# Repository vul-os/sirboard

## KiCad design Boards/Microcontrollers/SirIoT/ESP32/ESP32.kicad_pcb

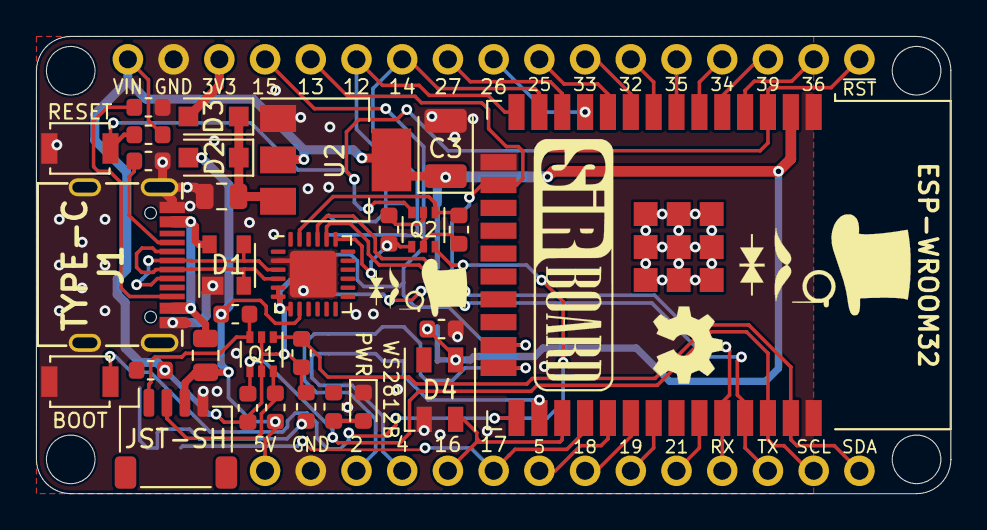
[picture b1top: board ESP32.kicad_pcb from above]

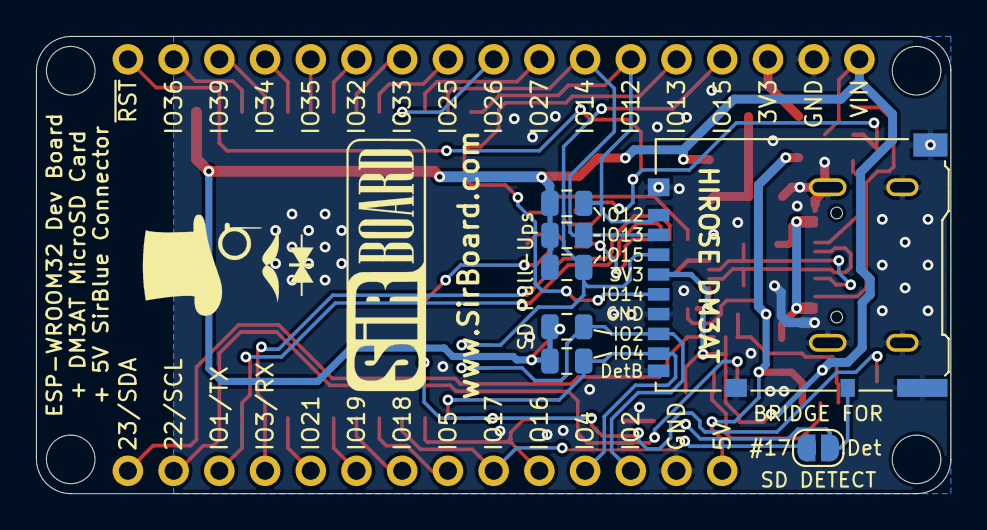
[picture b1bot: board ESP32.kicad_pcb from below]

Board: 2 copper layers, 50.8 x 25.4 mm, 43 parts (9 on the bottom side), 45 nets.

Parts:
BOOT: SW_Push; SW_SPST_B3U-1000P
C2: 10uF; C_0805_2012Metric
C3: 100uF; CP_EIA-3528-21_Kemet-B
C4: 1uF; C_0603_1608Metric
CARD1: SolderJumper_2_Open; SolderJumper-2_P1.3mm_Open_RoundedPad1.0x1.5mm
D1: PRTR5V0U2X; SOT-143
D2, D3: MBR120; D_SOD-123F
D4: WS2812B; WS2812B_MINI
DNP1, DNP2, DNP3, DNP4, DNP5: 47k; R_0805_2012Metric
F1: 500mA; Fuse_0805_2012Metric
H1, H2, H3, H4: MountingHole; MountingHole_2.7mm_M2.5
J1: TYPE-C; USB_C
J2: Micro_SD_Card_Det_Hirose_DM3AT; microSD_Hirose_DM3AT
J4: Conn_01x14; PinHeader_1x14_P2.54mm_Vertical
J5: Conn_01x17; PinHeader_1x17_P2.54mm_Vertical
JST-SH: SirBlue; SirBlue_Connector
PWR: RED; LED_0603_1608Metric
Q1: BSS138DW; SOT-363_SC-70-6
Q2: MMBT2222A; SOT-363_SC-70-6
R1, R2: 5K1; R_0603_1608Metric
R4, R5, R6, R7, R8, R9, R14, R17, R18: 10k; R_0603_1608Metric
R16: 1K; R_0603_1608Metric
RESET: SW_Push; SW_SPST_B3U-1000P
U1: CP2104; QFN-24-1EP_4x4mm_P0.5mm_EP2.6x2.6mm
U2: AZ1117-3.3; SOT-223-3_TabPin2
U3: ESP32-WROOM-32D; ESP32-WROOM-32

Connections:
#RST: J5.17, Q2.3, R14.2, RESET.1, U3.3
+3V3: C3.1, C4.1, D4.1, DNP1.1, DNP2.1, DNP3.1, DNP4.1, DNP5.1, J2.4, J5.1, Q1.2, Q1.5, R4.1, R6.1, R14.1, R16.1, R17.2, R18.2, U1.5, U1.6, U1.7, U2.2, U3.2
/CARD_DETECT: CARD1.2, J2.10, R17.1
/CC1: J1.A5, R2.1
/CC2: J1.B5, R1.1
D+: D1.3, J1.A6, J1.B6, U1.3
D-: D1.2, J1.A7, J1.B7, U1.4
DTR: Q2.1, R9.1, U1.23
GND: BOOT.1, C2.2, C3.2, C4.2, D1.1, D4.3, J1.A1, J1.A12, J1.B1, J1.B12, J1.S1, J2.6, J2.9, J2.11, J4.2, J5.2, JST-SH.4, PWR.1, R1.2, R2.2, RESET.2, U1.2, U1.25, U2.1, U3.1, U3.15, U3.38
IO0: BOOT.2, Q2.6, R18.1, U3.25
IO1_TX: J4.12, U1.20, U3.35
IO2_SD_D0: DNP2.2, J2.7, J4.3, U3.24
IO3_RX: J4.11, U1.21, U3.34
IO4_SD_D1: DNP1.2, J2.8, J4.4, U3.26
IO5_SD_CS: J4.7, U3.29
IO12_SD_D2: DNP5.2, J2.1, J5.6, U3.14
IO13_SD_D3: DNP4.2, J2.2, J5.7, U3.13
IO14_SD_CLK: J2.5, J5.5, U3.16
IO15_SD_CMD: DNP3.2, J2.3, J5.4, U3.23
IO16: D4.4, J4.5, U3.27
IO17_SD_DET: CARD1.1, J4.6, U3.28
IO18: J4.8, U3.30
IO19: J4.9, U3.31
IO21: J4.10, U3.33
IO22_SCL: J4.13, Q1.4, R6.2, U3.36
IO23_SDA: J4.14, Q1.1, R4.2, U3.37
IO25: J5.10, U3.10
IO26: J5.9, U3.11
IO27: J5.8, U3.12
IO32: J5.12, U3.8
IO33: J5.11, U3.9
IO34: J5.14, U3.6
IO35: J5.13, U3.7
IO36: J5.16, U3.4
IO39: J5.15, U3.5
unnamed: C2.1, D2.1, D3.1, U2.3
unnamed: PWR.2, R16.2
unnamed: Q2.2, R8.2
unnamed: Q2.5, R9.2
RTS: Q2.4, R8.1, U1.19
SCL_5V: JST-SH.1, Q1.3, R7.1
SDA_5V: JST-SH.2, Q1.6, R5.1
VBUS: D2.2, F1.2, J4.1, JST-SH.3, R5.2, R7.2, U1.8
VIN: D3.2, J5.3
VUSB: D1.4, F1.1, J1.A4, J1.A9, J1.B4, J1.B9

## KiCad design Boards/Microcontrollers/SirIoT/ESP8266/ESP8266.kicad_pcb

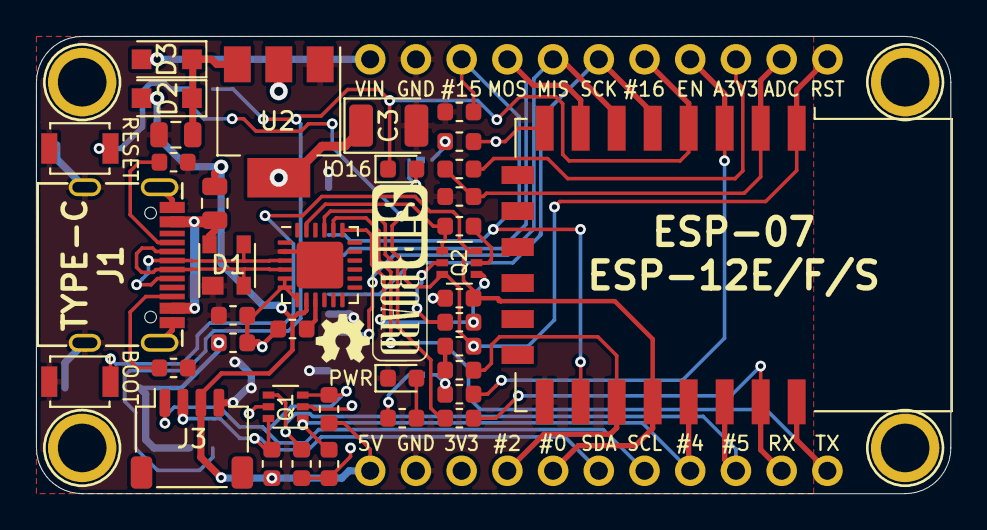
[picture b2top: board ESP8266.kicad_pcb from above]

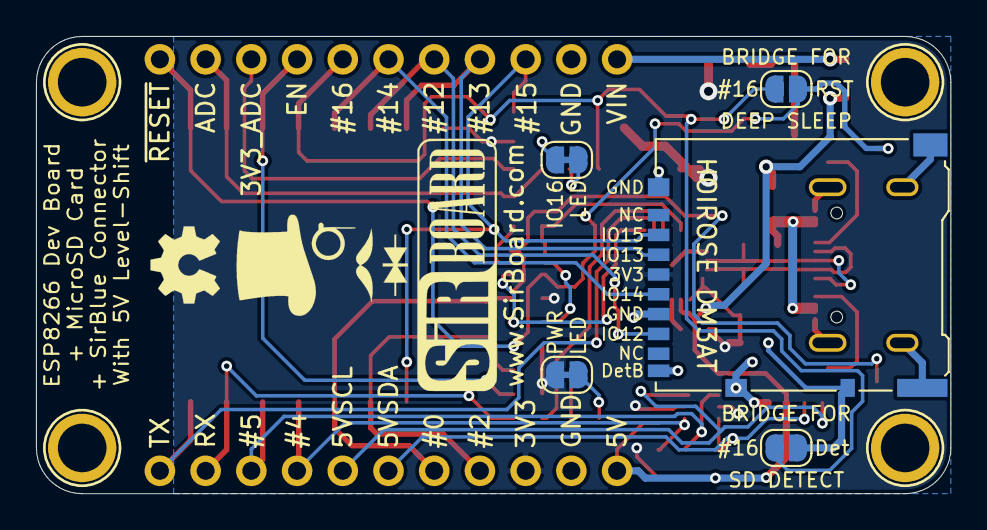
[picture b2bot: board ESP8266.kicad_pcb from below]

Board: 2 copper layers, 50.8 x 25.4 mm, 49 parts (7 on the bottom side), 38 nets.

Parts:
BOOT: SW_Push; SW_SPST_B3U-1000P
C1: 100nF; C_0603_1608Metric
C2: 10uF; C_0805_2012Metric
C3: 100uF; CP_EIA-3528-21_Kemet-B
CARD1: SolderJumper_2_Open; SolderJumper-2_P1.3mm_Open_RoundedPad1.0x1.5mm
D1: PRTR5V0U2X; SOT-143
D2, D3: MBR120; D_SOD-123F
F1: 500mA; Fuse_0805_2012Metric
H1, H2, H3, H4: MountingHole; MountingHole_M2.5_SirBoard
HOIROSE DM3AT: Micro_SD_Card_Det_Hirose_DM3AT; microSD_Hirose_DM3AT
IO16: LED_DELETE2; SolderJumper-2_P1.3mm_Bridged_RoundedPad1.0x1.5mm
IO16#2: BLUE; LED_0603_1608Metric
J1: TYPE-C; USB_C
J3: SirBlue; SirBlue_Connector
J4, J6: Conn_01x11; PinHeader_1x11_P2.54mm_Vertical
PWR: LED_DELETE1; SolderJumper-2_P1.3mm_Bridged_RoundedPad1.0x1.5mm
PWR#2: RED; LED_0603_1608Metric
Q1: BSS138DW; SOT-363_SC-70-6
Q2: MMBT2222A; SOT-363_SC-70-6
R1, R2: 5K1; R_0603_1608Metric
R3: 4K7; R_0603_1608Metric
R4, R5, R6, R7, R8, R9, R10, R11, R14, R17, R18: 10k; R_0603_1608Metric
R12, R15, R16: 1K; R_0603_1608Metric
R13: 10K; R_0603_1608Metric
R19: 220K; R_0603_1608Metric
R20: 100K; R_0603_1608Metric
RESET: SW_Push; SW_SPST_B3U-1000P
SLEEP1: SolderJumper_2_Open; SolderJumper-2_P1.3mm_Open_RoundedPad1.0x1.5mm
U1: CP2104; QFN-24-1EP_4x4mm_P0.5mm_EP2.6x2.6mm
U2: AZ1117-3.3; SOT-223-3_TabPin2
U3: ESP-12F; ESP-12E

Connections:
#RST: J6.11, Q2.3, R14.2, RESET.1, SLEEP1.2, U3.1
+3V3: C1.1, C3.1, HOIROSE DM3AT.4, J4.3, PWR.1, Q1.2, Q1.5, R3.2, R4.1, R6.1, R10.2, R11.2, R14.1, R15.1, R17.1, R18.2, U1.5, U1.6, U1.7, U2.2, U3.8
/CARD_DETECT: CARD1.2, HOIROSE DM3AT.10, R17.2
/CC1: J1.A5, R2.1
/CC2: J1.B5, R1.1
/RST: R3.1, U1.9
ADC: J6.10, R19.1, R20.2, U3.2
ADC_3V3: J6.9, R19.2
D+: D1.3, J1.A6, J1.B6, U1.3
D-: D1.2, J1.A7, J1.B7, U1.4
DTR: Q2.1, R9.1, U1.23
EN: J6.8, R10.1, U3.3
GND: BOOT.1, C1.2, C2.2, C3.2, D1.1, HOIROSE DM3AT.6, HOIROSE DM3AT.9, HOIROSE DM3AT.11, J1.A1, J1.A12, J1.B1, J1.B12, J1.S1, J3.4, J4.2, J6.2, PWR#2.1, R1.2, R2.2, R13.1, R20.1, RESET.2, U1.2, U1.25, U2.1, U3.15
GPIO0: BOOT.2, J4.5, Q2.6, R18.1, U3.18
GPIO2: J4.4, R11.1, U3.17
GPIO12_MISO: HOIROSE DM3AT.7, J6.5, U3.6
GPIO13_MOSI: HOIROSE DM3AT.3, J6.4, U3.7
GPIO14_SCK: HOIROSE DM3AT.5, J6.6, U3.5
GPIO15: HOIROSE DM3AT.2, J6.3, R13.2, U3.16
GPIO16: CARD1.1, IO16#2.1, J6.7, SLEEP1.1, U3.4
unnamed: C2.1, D2.1, D3.1, U2.3
unnamed: PWR.2, R16.1
unnamed: IO16.1, R15.2
unnamed: IO16.2, IO16#2.2
unnamed: PWR#2.2, R16.2
unnamed: Q2.2, R8.2
unnamed: Q2.5, R9.2
RTS: Q2.4, R8.1, U1.19
RXD: J4.10, R12.2, U3.21
RX_ESP: R12.1, U1.21
SCL_3V3: J4.9, Q1.4, R6.2, U3.20
SCL_5V: J3.1, J4.7, Q1.3, R7.1
SDA_3V3: J4.8, Q1.1, R4.2, U3.19
SDA_5V: J3.2, J4.6, Q1.6, R5.1
TX_ESP: J4.11, U1.20, U3.22
VBUS: D2.2, F1.2, J3.3, J4.1, R5.2, R7.2, U1.8
VIN: D3.2, J6.1
VUSB: D1.4, F1.1, J1.A4, J1.A9, J1.B4, J1.B9

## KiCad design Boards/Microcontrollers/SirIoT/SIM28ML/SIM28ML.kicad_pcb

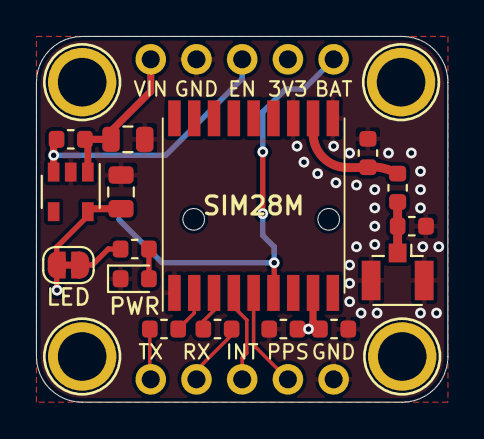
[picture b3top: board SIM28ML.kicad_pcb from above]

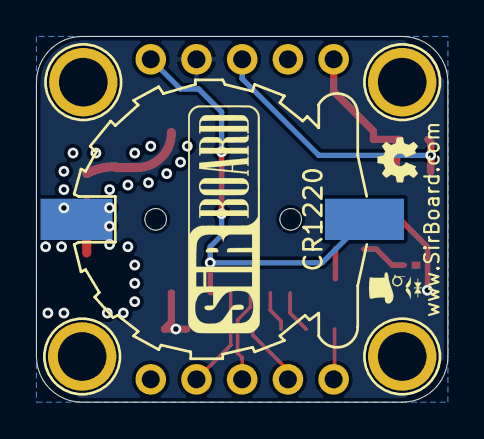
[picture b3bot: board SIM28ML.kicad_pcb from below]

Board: 2 copper layers, 22.9 x 20.3 mm, 23 parts (3 on the bottom side), 15 nets.

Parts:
AE1: Antenna_Shield; U.FL_Hirose_U.FL-R-SMT-1_Vertical
BT1: Battery_Cell; S8411-45R_1
C1: 4.7uF; C_0603_1608Metric
C2: 100nF; C_0603_1608Metric
C3, C4: 10uF; C_0805_2012Metric
C5, C7: NC; C_0603_1608Metric
H1, H2, H3, H4: MountingHole; MountingHole_M2.5_SirBoard
IC1: SIM28M
J1, J2: Conn_01x05; PinHeader_1x05_P2.54mm_Vertical
JP2: SolderJumper_2_Bridged; SolderJumper-2_P1.3mm_Bridged_RoundedPad1.0x1.5mm
PWR: LED; LED_0603_1608Metric
R1, R2: 100R; R_0603_1608Metric
R3: 10K; R_0603_1608Metric
R4: 0R; R_0603_1608Metric
R6: 680E; R_0603_1608Metric
U1: AP2127K-3.3; SOT-23-5

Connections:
3V3: C1.1, C2.1, C4.1, IC1.8, J2.4, JP2.1, U1.5
/ANT: C5.1, IC1.11, R4.1
EN: J2.3, R3.2, U1.3
GND: AE1.2, BT1.2, C1.2, C2.2, C3.2, C4.2, C5.2, C7.2, IC1.1, IC1.10, IC1.12, J1.5, J2.2, PWR.1, U1.2
INT: IC1.5, J1.4
unnamed: AE1.1, C7.1, R4.2
unnamed: PWR.2, R6.1
unnamed: IC1.2, R2.2
unnamed: IC1.3, R1.2
unnamed: JP2.2, R6.2
PPS: IC1.4, J1.3
RXD0: J1.2, R1.1
TXD0: J1.1, R2.1
VBAT: BT1.1, IC1.6, J2.5
VIN: C3.1, J2.1, R3.1, U1.1

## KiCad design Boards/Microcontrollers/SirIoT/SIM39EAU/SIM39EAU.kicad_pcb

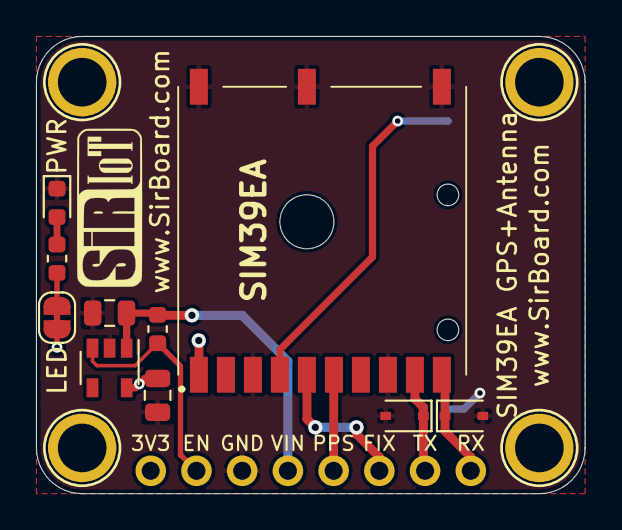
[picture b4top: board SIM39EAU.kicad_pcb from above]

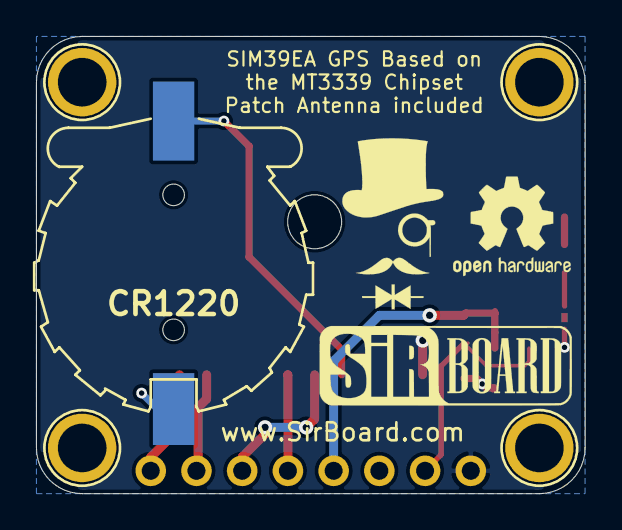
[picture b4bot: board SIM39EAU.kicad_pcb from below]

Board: 2 copper layers, 30.5 x 25.4 mm, 16 parts (2 on the bottom side), 11 nets.

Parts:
C3, C4: 10uF; C_0805_2012Metric
CR1220: CR1220; S8411-45R_1
D1, D2: TVS; D_SOD-323
H1, H2, H3, H4: MountingHole; MountingHole_M2.5_SirBoard
J1: Conn_01x08; PinHeader_1x08_P2.54mm_Vertical
LED: SolderJumper_2_Bridged; SolderJumper-2_P1.3mm_Bridged_RoundedPad1.0x1.5mm
PWR: LED; LED_0603_1608Metric
R1: 680E; R_0603_1608Metric
R3: 10K; R_0603_1608Metric
SIM39EA: SIM39EA
U1: AP2127K-3.3; SOT-23-5

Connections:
3V3: C4.1, J1.8, LED.1, SIM39EA.1, U1.5
EN: J1.7, R3.2, U1.3
FIX: J1.3, SIM39EA.5
GND: C3.2, C4.2, CR1220.2, D1.2, D2.2, J1.6, PWR.1, SIM39EA.3, SIM39EA.8, SIM39EA.11, SIM39EA.12, SIM39EA.13, U1.2
unnamed: CR1220.1, SIM39EA.4
unnamed: PWR.2, R1.1
unnamed: LED.2, R1.2
PPS: J1.4, SIM39EA.6
RX: D1.1, J1.1, SIM39EA.10
TX: D2.1, J1.2, SIM39EA.9
VIN: C3.1, J1.5, R3.1, U1.1

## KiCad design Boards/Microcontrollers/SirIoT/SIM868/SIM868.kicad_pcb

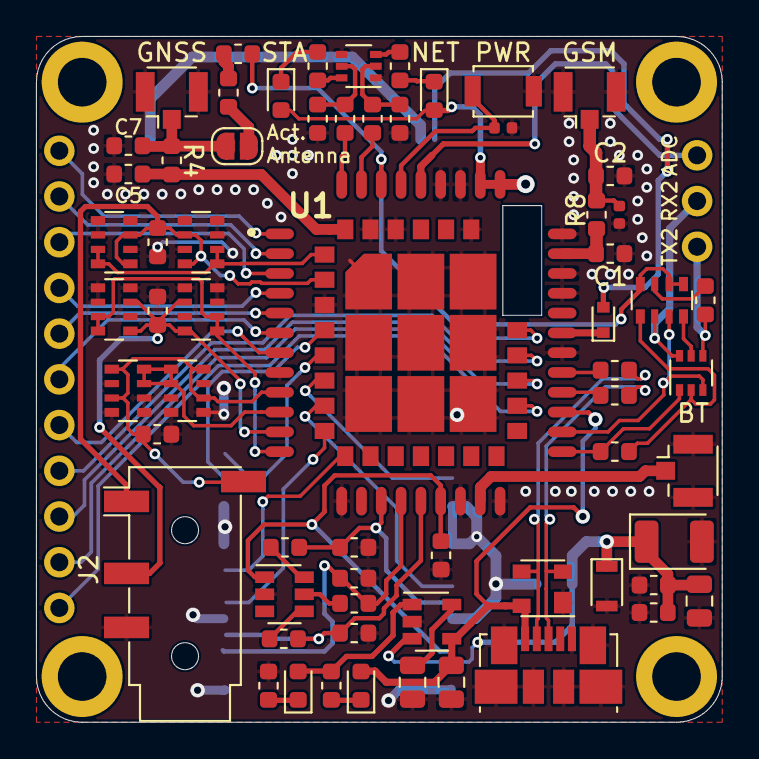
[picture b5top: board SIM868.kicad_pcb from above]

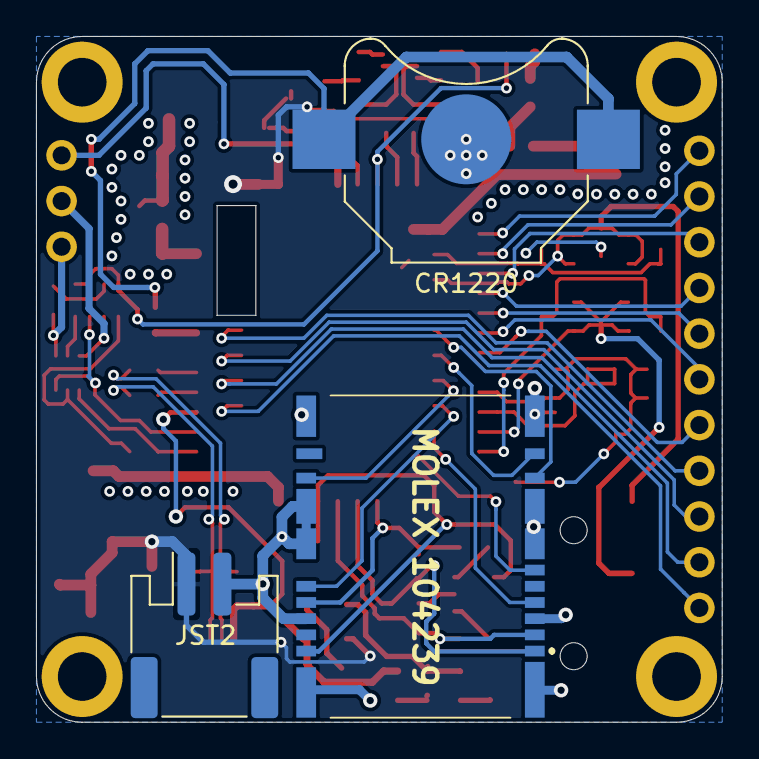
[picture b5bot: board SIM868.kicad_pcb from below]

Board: 2 copper layers, 38.1 x 38.1 mm, 73 parts (5 on the bottom side), 68 nets.

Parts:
BT: Antenna_Shield; U.FL_Hirose_U.FL-R-SMT-1_Vertical
C1, C2, C5, C7: NC; C_0603_1608Metric
C3: 100nF; C_0603_1608Metric
C4: 100uF; CP_EIA-3528-21_Kemet-B
C6: 10uF; C_0805_2012Metric
C8: 33pF; C_0603_1608Metric
C9: 10pF; C_0603_1608Metric
C10, C11, C12: 22pF; C_0603_1608Metric
C13: 1uF; C_0805_2012Metric
CN1, CN2, CN3: 10pF; R_Array_Convex_4x0603
CN4, CN5, CN6: 33pF; R_Array_Convex_4x0603
CR1220: CR1025; BatteryHolder_Keystone_3000_1x12mm
D1: ESDA6V1-5SC6; SOT-23-6
D3: D_Schottky; D_SOD-523
D5: ORANGE; LED_0603_1608Metric
D6: GREEN; LED_0603_1608Metric
D7: PRTR5V0U2X; SOT-143
D9, D11, D13: BDFN1C031V; C_0603_1608Metric
GNSS: Antenna_Shield; U.FL_Hirose_U.FL-R-SMT-1_Vertical
GSM: Antenna_Shield; U.FL_Hirose_U.FL-R-SMT-1_Vertical
H1, H2, H3, H4: MountingHole; MountingHole_2.7mm_M2.5_ISO14580_Pad
J2: AudioJack4; Jack_3.5mm_PJ320D_Horizontal
J4: USB_B_Micro; USB_Micro-B_Molex_47346-0001
J5: Conn_01x11; PinHeader_1x11_P2.54mm_Vertical
J6: Conn_01x03; PinHeader_1x03_P2.54mm_Vertical
JP1: SolderJumper_2_Open; SolderJumper-2_P1.3mm_Open_RoundedPad1.0x1.5mm
JST2: Conn_01x02; JST_PH_S2B-PH-SM4-TB_1x02-1MP_P2.00mm_Horizontal
L1: 27n; L_0603_1608Metric
MOLEX 104239: MOLEX 104239-1430; 1042391430
NET: WHITE; LED_0603_1608Metric
PWR: B3U-1000P; SW_SPST_B3U-1000P
Q1, Q2: BC847BDW1; SOT-363_SC-70-6
R1, R6, R13, R16: 47K; R_0603_1608Metric
R2: 2K; R_0805_2012Metric
R3, R14, R17: 1K; R_0603_1608Metric
R4, R8: 0R; R_0603_1608Metric
R5: 10R; R_0603_1608Metric
R7: 470E; R_0603_1608Metric
R9, R10, R11: 51E; R_0603_1608Metric
R12, R15: 4K7; R_0603_1608Metric
R18, R19: 22E; R_0603_1608Metric
RN2: 4k7; R_Array_Convex_4x0603
STA: WHITE; LED_0603_1608Metric
TVS1, TVS2: LXES15AAA1-153; R_0402_1005Metric
U1: SIM868
U2: MCP73831-2-OT; SOT-23-5
Z1: PZ3D4V2H; D_SOD-323F

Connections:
5V: R6.2, RN2.7
/BT: BT.1, U1.20
/uD+: R18.1, U1.25
/uD-: R19.1, U1.26
ADC: J6.3, U1.38
D+: D7.2, J4.3, R18.2
D-: D7.3, J4.2, R19.2
GND: BT.2, C1.2, C2.2, C3.2, C4.2, C5.2, C6.2, C7.2, C8.2, C9.2, C10.2, C11.2, C12.2, C13.2, CN1.2, CN1.4, CN1.5, CN1.6, CN2.2, CN2.4, CN2.5, CN2.6, CN3.2, CN3.4, CN3.5, CN3.6, CN4.3, CN4.4, CN4.5, CN4.7, CN5.3, CN5.4, CN5.5, CN5.7, CN6.3, CN6.4, CN6.5, CN6.7, CR1220.2, D1.2, D7.1, D9.1, D11.1, D13.1, GNSS.2, GSM.2, J2.R2, J4.5, J4.6, JST2.2, MOLEX 104239.4, MOLEX 104239.12, MOLEX 104239.15, MOLEX 104239.16, MOLEX 104239.17, MOLEX 104239.18, MOLEX 104239.19, MOLEX 104239.20, MOLEX 104239.21, MOLEX 104239.22, PWR.1, Q2.1, Q2.4, R2.1, R3.2, R13.1, R16.1, TVS1.1, TVS2.1, U1.8, U1.13, U1.19, U1.21, U1.27, U1.30, U1.31, U1.33, U1.36, U1.37, U1.45, U1.63, U1.66, U1.67, U1.69, U1.70, U1.71, U1.72, U1.73, U1.74, U1.75, U1.76, U1.77, U2.2, Z1.2
GNSS_ANT: C5.1, R4.1, U1.68
GNSS_EN: J5.11, U1.59
GNSS_RX: J5.8, U1.62
GNSS_TX: J5.9, U1.61
GSM_ANT: C1.1, R8.1, U1.32
MIC+: CN1.1, CN1.3, CN4.6, CN4.8, D11.2, J2.S, U1.9
MIC-: CN1.7, CN1.8, CN4.1, CN4.2, U1.10
NET_L: R12.2, U1.41
unnamed: C7.1, GNSS.1, JP1.2, R4.2
unnamed: C2.1, GSM.1, R8.2, TVS2.2
unnamed: CR1220.1, D3.2
unnamed: D1.4, R9.1
unnamed: D1.5, R10.1
unnamed: D1.6, R11.1
unnamed: R14.2, STA.1
unnamed: D3.1, U1.28
unnamed: NET.1, R17.2
unnamed: D5.1, R7.2
unnamed: D6.1, R3.1
unnamed: D6.2, R7.1, U2.1
unnamed: JP1.1, L1.1
unnamed: L1.2, R5.2
unnamed: Q1.2, R1.2, RN2.1
unnamed: Q1.5, RN2.4
unnamed: Q2.2, R12.1, R13.2
unnamed: Q2.3, R17.1
unnamed: Q2.5, R15.1, R16.2
unnamed: Q2.6, R14.1
unnamed: R2.2, U2.5
PPS: J5.10, U1.60
PWR_KEY: PWR.2, TVS1.2, U1.39
RX_5V: J6.2, Q1.6, RN2.2
SD_CLK: MOLEX 104239.11, U1.50
SD_CMD: MOLEX 104239.9, U1.51
SD_DATA0: MOLEX 104239.13, U1.49
SD_DATA1: MOLEX 104239.14, U1.48
SD_DATA2: MOLEX 104239.7, U1.47
SD_DATA3: MOLEX 104239.8, U1.46
SIM_CLK: C11.1, MOLEX 104239.1, R10.2, U1.16
SIM_IO: C10.1, MOLEX 104239.6, R11.2, U1.15
SIM_RST: C12.1, MOLEX 104239.2, R9.2, U1.17
SIM_VDD: C3.1, D1.1, MOLEX 104239.3, U1.18
SPK1+: CN2.1, CN2.3, CN5.6, CN5.8, D9.2, J2.R1, U1.11
SPK1-: CN2.7, CN2.8, CN5.1, CN5.2, U1.12
SPK2+: CN3.1, CN3.3, CN6.6, CN6.8, D13.2, J2.T, U1.44
SPK2-: CN3.7, CN3.8, CN6.1, CN6.2, U1.43
STA_L: R15.2, U1.42
TX_5V: J6.1, Q1.4, R6.1
UART1_CTS: J5.4, U1.4
UART1_DCD: J5.5, U1.5
UART1_DTR: J5.6, U1.6
UART1_RI: J5.7, U1.7
UART1_RTS: J5.3, U1.3
UART1_RX: J5.2, U1.2
UART1_TX: J5.1, U1.1
UART2_RX: Q1.3, RN2.3, U1.23
UART2_TX: Q1.1, R1.1, U1.22
VBAT: C4.1, C6.1, C8.1, C9.1, JST2.1, NET.2, STA.2, U1.34, U1.35, U2.3, Z1.1
VBUS: C13.1, D5.2, D7.4, J4.1, U1.24, U2.4
VCC_EXT: R5.1, RN2.5, RN2.6, RN2.8, U1.40

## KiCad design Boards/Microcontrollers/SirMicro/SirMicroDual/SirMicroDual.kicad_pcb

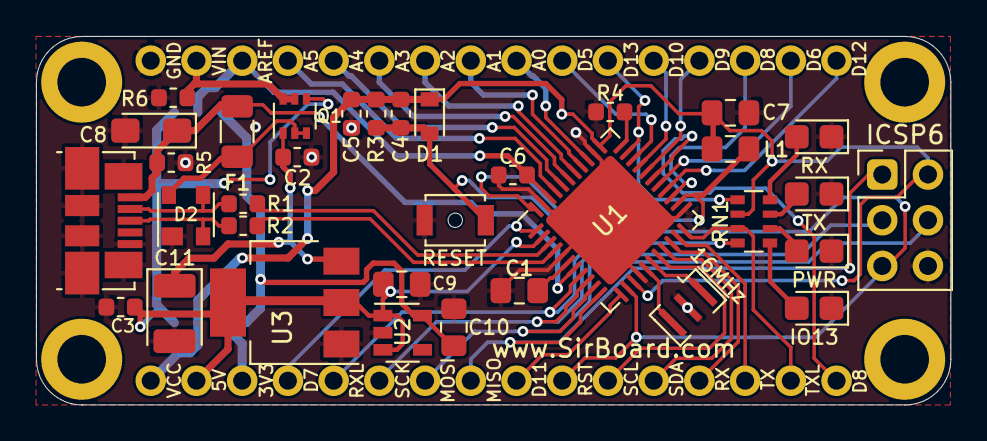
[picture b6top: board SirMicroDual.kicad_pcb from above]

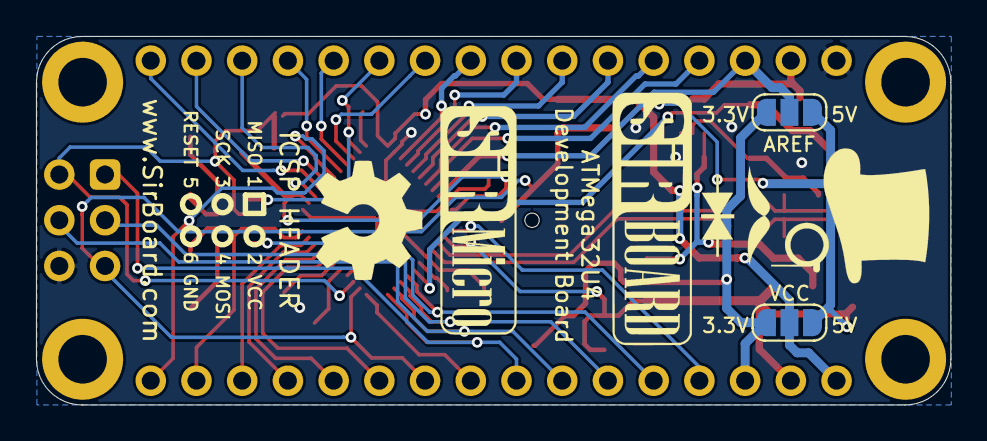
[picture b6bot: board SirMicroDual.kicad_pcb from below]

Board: 2 copper layers, 50.8 x 20.5 mm, 38 parts (4 on the bottom side), 48 nets.

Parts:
16MHz: 16MHz; Resonator_SMD_muRata_CSTxExxV-3Pin_3.0x1.1mm
C1, C7, C9, C10: 1uF; C_0805_2012Metric_Pad1.15x1.40mm_HandSolder
C2, C3, C4, C5, C6: 100nF; C_0603_1608Metric
C8: 22uF; CP_EIA-3216-18_Kemet-A_Pad1.58x1.35mm_HandSolder
C11: 22uF; CP_EIA-3528-12_Kemet-T
D1: D; D_SOD-110
D2: PRTR5V0U2X; SOT-143
F1: 500mA; R_1206_3216Metric
ICSP6: Conn_02x03_Odd_Even; PinHeader_2x03_P2.54mm_Vertical
IO13: LED; LED_0805_2012Metric_Castellated
J1, J2: Conn_01x16; PinHeader_1x16_P2.54mm_Vertical
J3: USB_B_Micro; USB_Micro-B_Molex_47346-0001
JP1, JP2: SolderJumper_3_Open; SolderJumper-3_P1.3mm_Open_RoundedPad1.0x1.5mm
L1: 10uH; L_0805_2012Metric_Pad1.15x1.40mm_HandSolder
PWR: LED; LED_0805_2012Metric_Castellated
Q1: DMP2004DWK-7; SOT-363_SC-70-6
R1, R2: 22e; R_0603_1608Metric
R3, R4, R5, R6: 10k; R_0603_1608Metric
RESET: SW_Push; SW_SPST_B3U-1000P-B
RN1: 1k; R_Array_Convex_4x0603
RX: LED; LED_0805_2012Metric_Castellated
TX: LED; LED_0805_2012Metric_Castellated
U1: ATmega32U4-MU; QFN-44-1EP_7x7mm_P0.5mm_EP5.2x5.2mm
U2: AP2127K-3.3; SOT-23-5
U3: AZ1117-5.0; SOT-223-3_TabPin2

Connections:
3V3: C10.1, J2.3, JP1.3, JP2.3, U2.5
5V: C3.1, C9.1, J2.2, JP1.1, JP2.1, Q1.4, U1.2, U2.1, U2.3, U3.2
/HWB: R4.1, U1.33
/X1: 16MHz.1, U1.17
/X2: 16MHz.3, U1.16
/uD+: R2.2, U1.4
/uD-: R1.2, U1.3
A0: J1.9, U1.36
A1: J1.8, U1.37
A2: J1.7, U1.38
A3: J1.6, U1.39
A4: J1.5, U1.40
A5: J1.4, U1.41
AREF: C6.1, J1.3, JP2.2, U1.42
D4: J1.14, U1.25
D5: J1.10, U1.31
D6: J1.15, U1.27
D7: J2.4, U1.1
D8: J2.16, U1.28
D9: J1.13, U1.29
D10: J1.12, U1.30
D11: J2.9, U1.12
D12: J1.16, U1.26
D13: J1.11, RN1.1, U1.32
D+: D2.2, J3.3, R2.1
D-: D2.3, J3.2, R1.1
GND: 16MHz.2, C1.2, C2.2, C3.2, C5.2, C6.2, C7.2, C8.2, C9.2, C10.2, C11.2, D2.1, ICSP6.6, IO13.1, J1.1, J3.5, J3.6, PWR.1, R4.2, R5.2, R6.2, RESET.1, RX.1, TX.1, U1.5, U1.15, U1.23, U1.35, U1.43, U1.45, U2.2, U3.1
MISO: ICSP6.1, J2.8, U1.11
MOSI: ICSP6.4, J2.7, U1.10
unnamed: C1.1, U1.6
unnamed: C8.1, F1.2, J3.1, R5.1, U1.7
unnamed: C2.1, C11.1, Q1.1, U3.3
unnamed: IO13.2, RN1.5
unnamed: L1.2, U1.24, U1.44
unnamed: PWR.2, RN1.6
unnamed: RN1.7, TX.2
unnamed: RN1.8, RX.2
RST: C4.2, D1.2, ICSP6.5, J2.10, R3.2, RESET.2, U1.13
RX: J2.13, U1.20
RXLED: J2.5, RN1.4, U1.8
SCK: ICSP6.3, J2.6, U1.9
SCL: J2.11, U1.18
SDA: J2.12, U1.19
TX: J2.14, U1.21
TXLED: J2.15, RN1.3, U1.22
VCC: C4.1, C5.1, C7.1, D1.1, ICSP6.2, J2.1, JP1.2, L1.1, R3.1, RN1.2, U1.14, U1.34
VIN: J1.2, Q1.5, Q1.6, R6.1
VUSB: D2.4, F1.1, Q1.2, Q1.3

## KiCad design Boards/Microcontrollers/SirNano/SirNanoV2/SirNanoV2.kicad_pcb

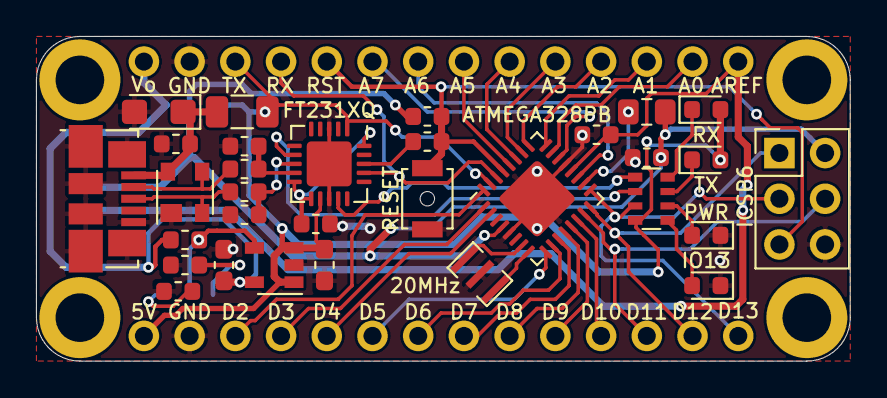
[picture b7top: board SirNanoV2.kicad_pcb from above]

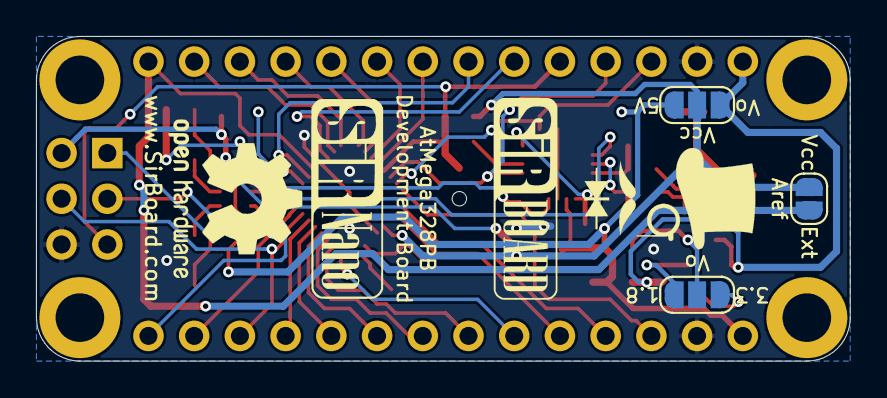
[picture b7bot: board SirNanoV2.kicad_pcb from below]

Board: 2 copper layers, 45.2 x 18.0 mm, 36 parts (5 on the bottom side), 47 nets.

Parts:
20MHz: 20MHz; Resonator_SMD_muRata_CSTxExxV-3Pin_3.0x1.1mm
C1, C3, C11: 100nF; C_0603_1608Metric
C2, C4: 47pF; C_0603_1608Metric
C6: 10nF; C_0603_1608Metric
C7: 1uF; C_0603_1608Metric
C8: 22uF; CP_EIA-3216-12_Kemet-S
C9, C10: 1uF; C_0603_1608Metric_Pad1.05x0.95mm_HandSolder
D1: PRTR5V0U2X; SOT-143
F1: 500mA; R_1206_3216Metric
FT231XQ: FT231XQ; QFN-20-1EP_4x4mm_P0.5mm_EP2.5x2.5mm
ICSP6: Conn_02x03_Odd_Even; PinHeader_2x03_P2.54mm_Vertical
IO13: LED; LED_0603_1608Metric
J1, J2: Conn_01x14; PinHeader_1x14_P2.54mm_Vertical
J3: USB_B_Micro; USB_Micro-B_Molex_47346-0001
JP1: SolderJumper_2_Bridged; SolderJumper-2_P1.3mm_Open_RoundedPad1.0x1.5mm
JP2, JP3: SolderJumper_3_Open; SolderJumper-3_P1.3mm_Open_RoundedPad1.0x1.5mm
L1: 10uH; L_0805_2012Metric_Pad1.15x1.40mm_HandSolder
PWR: LED; LED_0603_1608Metric
R1, R2: 27e; R_0603_1608Metric
R3: 10k; R_0603_1608Metric
R5: 56k; R_0603_1608Metric
R6: 22k; R_0603_1608Metric
R7: 68k; R_0603_1608Metric
RESET: SW_Push; SW_SPST_B3U-1000P-B
RN1: R_Pack04; R_Array_Convex_4x0603
RX: LED; LED_0603_1608Metric
TX: LED; LED_0603_1608Metric
U1: ATmega328PB-MU; QFN-32-1EP_5x5mm_P0.5mm_EP3.1x3.1mm
U2: AP7365-ADJ; SOT-23-5

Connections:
1.8V: JP2.3, R5.1
3.3V: C3.1, FT231XQ.10, FT231XQ.11, FT231XQ.20
3_3V: JP2.1, R6.1
5V: C9.1, F1.1, FT231XQ.12, J1.1, JP3.3, RN1.4, RX.2, TX.2, U2.1, U2.3
/IO13LED: IO13.2, RN1.5
/PWRLED: PWR.2, RN1.6
/X1: 20MHz.3, U1.7
/X2: 20MHz.1, U1.8
/uD+: C2.1, FT231XQ.8, R2.2
/uD-: C4.1, FT231XQ.9, R1.2
A0: J2.13, U1.23
A1: J2.12, U1.24
A2: J2.11, U1.25
A3: J2.10, U1.26
A4: J2.9, U1.27
A5: J2.8, U1.28
A6: J2.7, U1.19
A7: J2.6, U1.22
ADJ: JP2.2, R7.2, U2.4
AREF: C1.1, J2.14, JP1.1, U1.20
D2: J1.3, U1.32
D3: J1.4, U1.1
D4: J1.5, U1.2
D5: J1.6, U1.9
D6: J1.7, U1.10
D7: J1.8, U1.11
D8: J1.9, U1.12
D9: J1.10, U1.13
D10: J1.11, U1.14
D11: ICSP6.4, J1.12, U1.15
D12: ICSP6.1, J1.13, U1.16
D13: ICSP6.3, J1.14, RN1.3, U1.17
D+: D1.2, J3.3, R2.1
D-: D1.3, J3.2, R1.1
GND: 20MHz.2, C1.2, C2.2, C3.2, C4.2, C6.2, C7.2, C8.2, C9.2, C10.2, D1.1, FT231XQ.3, FT231XQ.13, FT231XQ.21, ICSP6.6, IO13.1, J1.2, J2.2, J3.5, J3.6, PWR.1, R5.2, R6.2, RESET.2, U1.5, U1.21, U1.33, U2.2
unnamed: C11.2, FT231XQ.18
unnamed: L1.2, U1.18
unnamed: RN1.7, TX.1
unnamed: RN1.8, RX.1
RESET: C11.1, ICSP6.5, J2.5, R3.2, RESET.1, U1.29
RX: FT231XQ.17, J2.4, U1.30
RX_LED: FT231XQ.14, RN1.1
TX: FT231XQ.1, J2.3, U1.31
TX_LED: FT231XQ.7, RN1.2
VBUS: C6.1, C8.1, D1.4, F1.2, J3.1
VCC: C7.1, ICSP6.2, JP1.2, JP3.2, L1.1, R3.1, U1.4
VOUT: C10.1, J2.1, JP3.1, R7.1, U2.5
